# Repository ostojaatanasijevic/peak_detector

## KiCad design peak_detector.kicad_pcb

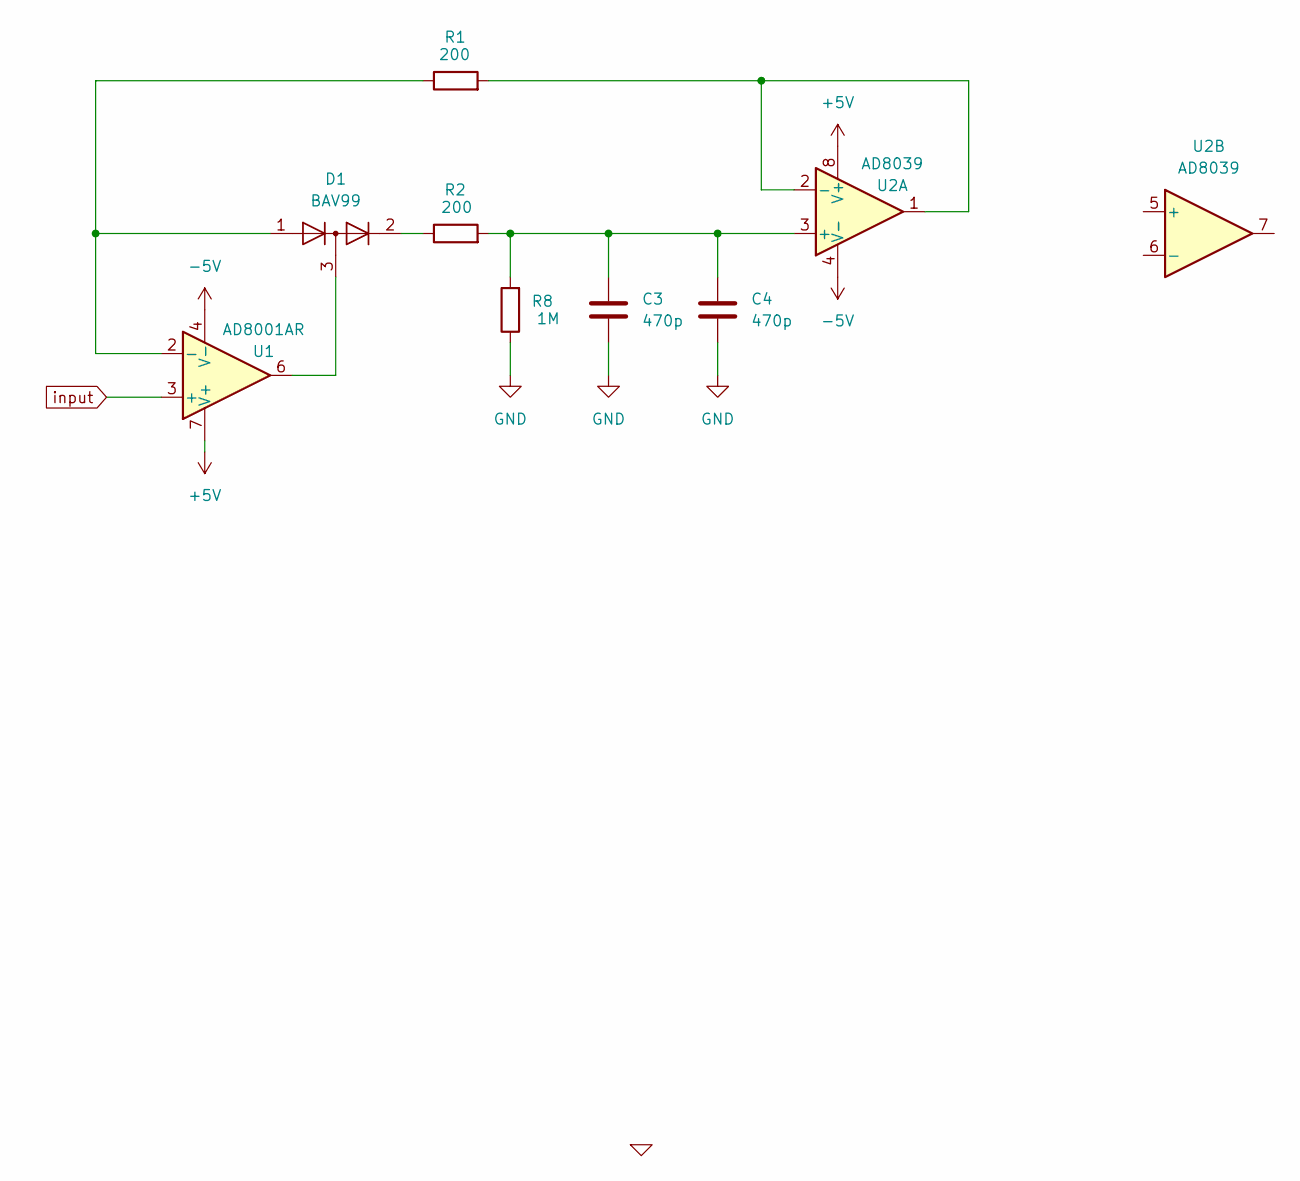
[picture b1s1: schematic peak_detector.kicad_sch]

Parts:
C3, C4: 470p; C_0603_1608Metric_Pad1.08x0.95mm_HandSolder
D1: BAV99; SOT-23
R1, R2: 200; R_0603_1608Metric_Pad0.98x0.95mm_HandSolder
R8: 1M; R_0603_1608Metric_Pad0.98x0.95mm_HandSolder
U1: AD8001AR; SOIC-8_3.9x4.9mm_P1.27mm
U2: AD8039; SOIC-8_3.9x4.9mm_P1.27mm

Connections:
+5V: U1.7 (V+), U2.8 (V+)
-5V: U1.4 (V-), U2.4 (V-)
GND: C3.2, C4.2, R8.1
unnamed: D1.2 (A), R2.1
unnamed: D1.3 (K), U1.6
unnamed: D1.1 (K), R1.1, U1.2 (-)
unnamed: C3.1, C4.1, R2.2, R8.2, U2.3 (+)
unnamed: R1.2, U2.1, U2.2 (-)
input: U1.3 (+)

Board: 2 copper layers, 8 parts (0 on the bottom side), 8 nets, no tracks yet.

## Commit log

2024-11-11 init
2024-11-11 Reorder.
2024-11-11 Sims.
2024-11-14 Dual bjt and MIC920.
2024-11-14 Idk.
